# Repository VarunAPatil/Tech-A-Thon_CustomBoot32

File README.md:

# Tech-A-Thon_CustomBoot32

# Tech-A-Thon_CustomBoot32

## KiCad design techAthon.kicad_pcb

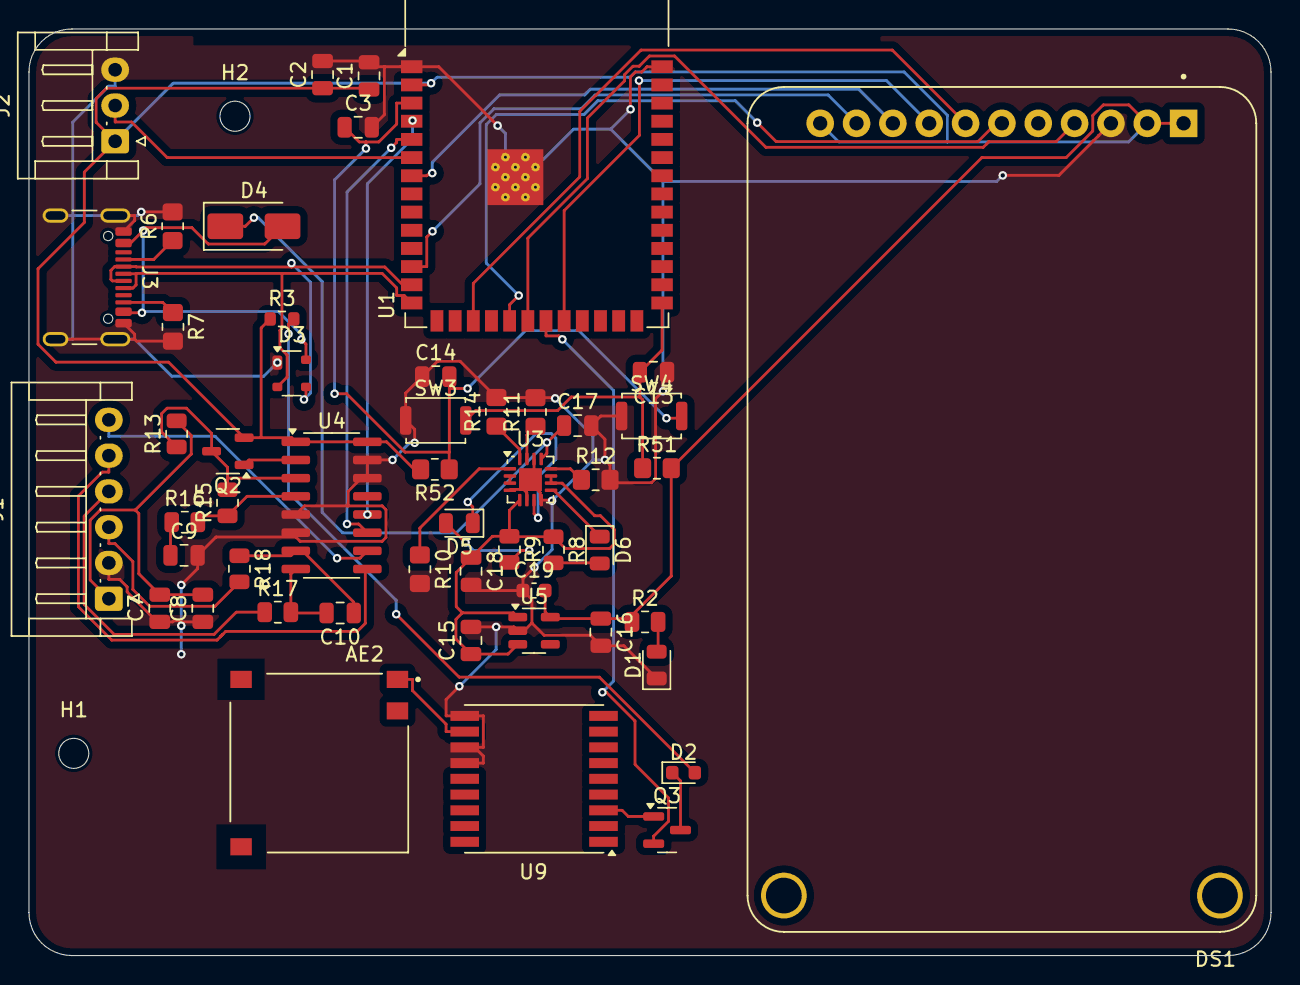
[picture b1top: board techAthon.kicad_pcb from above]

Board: 2 copper layers, 86.8 x 64.8 mm, 53 parts (0 on the bottom side), 46 nets.

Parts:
AE2: 1575R-A; XDCR_PRO-OB-430
C1, C3, C13, C14: 0.1uF; C_0805_2012Metric
C2, C15, C16: 22uF; C_0805_2012Metric
C7, C9, C10: 100n; C_0805_2012Metric
C8: 10u; C_0805_2012Metric
C17: 1uF; C_0805_2012Metric
C18: 4.7uF; C_0805_2012Metric
C19: 100nF; C_0603_1608Metric
D1, D5, D6: LED; LED_0805_2012Metric
D2: BLUE; LED_0603_1608Metric
D3: SP0503BAHT; SOT-143
D4: SS14; D_SMA
DS1: TFT SPI LCD DISPLAY; MODULE_4311
H1, H2: MountingHole; MountingHole_2.1mm
J1: LOAD_CELL; JST_EH_S6B-EH_1x06_P2.50mm_Horizontal
J2: TEMPERATURE SENSOR; JST_EH_S3B-EH_1x03_P2.50mm_Horizontal
J3: USB_C_Receptacle_USB2.0_16P; USB_C_Receptacle_GCT_USB4105-xx-A_16P_TopMnt_Horizontal
Q2: MMBT4403; SOT-23-3
Q3: SI2302; SOT-23
R2: 0.3k; R_0805_2012Metric
R3: 10k; R_0603_1608Metric
R6, R7: 5.1K; R_0805_2012Metric_Pad1.20x1.40mm_HandSolder
R8, R9: 1.5k; R_0805_2012Metric
R10: 10k; R_0805_2012Metric_Pad1.20x1.40mm_HandSolder
R11: 4.12k; R_0805_2012Metric_Pad1.20x1.40mm_HandSolder
R12: 1.18k; R_0805_2012Metric_Pad1.20x1.40mm_HandSolder
R13: 10R; R_0805_2012Metric
R14: 1.13k; R_0805_2012Metric_Pad1.20x1.40mm_HandSolder
R15: 20k; R_0805_2012Metric
R16: 8k2; R_0805_2012Metric
R17, R18: 100R; R_0805_2012Metric
R51, R52: 10K; R_0805_2012Metric_Pad1.20x1.40mm_HandSolder
SW3: SW_0; SW_Push_SPST_NO_Alps_SKRK
SW4: SW_EN; SW_Push_SPST_NO_Alps_SKRK
U1: ESP32-S3-WROOM-1
U3: BQ24074RGT; VQFN-16-1EP_3x3mm_P0.5mm_EP1.6x1.6mm
U4: HX711; SOP-16_3.9x9.9mm_P1.27mm
U5: TLV75533PDBV; SOT-23-5
U9: SIM28; SIM28ML

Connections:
/0: C13.2, R51.1, SW3.2, U1.27 (IO0)
/3V3: C1.1, C2.1, C16.1, C19.2, DS1.1 (VIN), DS1.2 (3VO), DS1.11 (BACKLIGHT), J2.1, Q2.2 (E), R2.1, R3.1, R51.2, R52.2, U1.2 (3V3), U4.1 (VSUP), U4.16 (DVDD), U5.5 (OUT)
/5V: C17.1, D4.1 (K), U3.13 (IN)
/A+: J1.4, R17.1
/A-: J1.3, R18.2
/B+: J1.6, U4.10 (INB+)
/B-: J1.5, U4.9 (INB-)
/BAT+: U3.2 (BAT), U3.3 (BAT)
/BAT_OUT: C15.1, C18.1, R8.1, R9.1, U3.5 (EN2), U3.10 (OUT), U3.11 (OUT), U5.1 (IN), U5.3 (EN)
/CS: DS1.7 (CS), U1.17 (IO9)
/D+: D3.2 (K), J3.A6 (D+), J3.B6 (D+), U1.14 (USB_D+)
/D-: D3.3 (K), J3.A7 (D-), J3.B7 (D-), U1.13 (USB_D-)
/DATA: J2.2, U1.6 (IO6)
/DT: U1.4 (IO4), U4.12 (DOUT)
/D/C: DS1.9 (D/C), U1.7 (IO7)
/E+: C7.2, C8.2, J1.1, R13.2
/EN: C3.1, C14.2, R52.1, SW4.2, U1.3 (EN)
/GPS_LED: Q3.2 (S), U1.21 (IO13)
/MOSI_D: DS1.6 (MOSI), U1.19 (IO11)
/RST: DS1.8 (~RST), U1.22 (IO14)
/SCK: U1.5 (IO5), U4.11 (PD_SCK)
/SCK_D: DS1.4 (SCK), U1.20 (IO12)
/SDCS: DS1.10 (SDCS), U1.12 (IO8)
/VBUS: D3.4 (K), D4.2 (A), J3.A4 (VBUS), J3.A9 (VBUS), J3.B4 (VBUS), J3.B9 (VBUS)
GND: C1.2, C2.2, C3.2, C7.1, C8.1, C9.2, C13.1, C14.1, C15.2, C16.2, C17.2, C18.2, C19.1, D1.1 (K), D3.1 (A), DS1.3 (GND), J1.2, J2.3, J3.A1 (GND), J3.A12 (GND), J3.B1 (GND), J3.B12 (GND), J3.S1 (SHIELD), R6.2, R7.2, R10.2, R11.2, R12.2, R14.2, SW3.1, SW4.1, U1.1 (GND), U1.40 (GND), U1.41 (GND), U3.4 (~CE), U3.6 (EN1), U3.8 (VSS), U3.14 (TMR), U3.17 (VSS), U4.5 (AGND), U4.6 (VBG), U4.14 (XI), U4.15 (RATE), U5.2 (GND), U9.10 (GND), U9.12 (GND), U9.13 (GND)
unnamed: AE2.1 (A), U9.11 (RF_IN)
unnamed: C9.1, R16.1
unnamed: D1.2 (A), R2.2
unnamed: D2.2 (A), R3.2
unnamed: D2.1 (K), Q3.3 (D)
unnamed: D5.2 (A), R9.2
unnamed: D5.1 (K), U3.7 (~PGOOD)
unnamed: D6.2 (A), R8.2
unnamed: D6.1 (K), U3.9 (~CHG)
unnamed: J3.A5 (CC1), R6.1
unnamed: J3.B5 (CC2), R7.1
unnamed: Q2.1 (B), U4.2 (BASE)
unnamed: Q2.3 (C), R13.1, R15.2, U4.3 (AVDD)
unnamed: Q3.1 (G), U9.3 (TIMEMARK)
unnamed: R12.1, U3.12 (ILIM)
unnamed: R14.1, U3.16 (ISET)
unnamed: R11.1, U3.15 (ITERM)
unnamed: R10.1, U3.1 (TS)
unnamed: C10.2, R17.2, U4.8 (INA+)
unnamed: C10.1, R18.1, U4.7 (INA-)
unnamed: R15.1, R16.2, U4.4 (VFB)

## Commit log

2026-02-26 Sensor codes
2026-02-26 Remove build and config files from repo
2026-02-26 Kept backup gps code and created load cell project
2026-02-26 added load cell
2026-02-26 Branch Creation
2026-02-26 Peltier Module Control Added
2026-02-26 integrating Temp and load cell
2026-02-26 Added Display to monitor
2026-02-26 Added a custom font
2026-02-26 added lcd display support (LVGL)
2026-02-26 Added SELF OTA feature
2026-02-26 Integrated firebase and logged temp, cell count & coordinates
2026-02-27 Implemented sensor syncing using freeRTOS and changed structure of firebase data
2026-02-27 Cleaned Repository
2026-02-28 Added pwm codes for graph plotting
2026-05-03 Build folders removed
2026-05-03 Removed sdkconfig files
2026-05-03 Resolving merge conflicts
2026-05-03 Firmware Updated
